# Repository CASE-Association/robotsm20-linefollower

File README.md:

# Blitz V2
Project repository for the line follower **Blitz V2** to compete in Robot SM 2020. Last years robot was [Blitz V1](https://github.com/caselabbet/robotsm19-linefollower).

Below is a rendered version of **Blitz V2**.

## Goals 
- Utilize more advanced control algorithm.
    - Acceleration control
        - Speed trajectory planner
    - Speed control
        - PID + Anti windup + Active damping
    - Position control
        - PID + Anti windup + Active damping
    - State space model + LQG controller (*optional*)
    - MPC - Model Predictive Conrol (*optional)*
- Map race track + Path planner (*optional*)
- Beat last years result and take 1st place. (*not optional*) 
- Added hardware and improvements
    - Use of suction/exhuast fans
    - Single PCB
    - Bluetooth communication
    - High power motors (11W vs 1/2W)
 
## Directories 
```
robotsm20-linefollower
├── datasheets      
├── hardware        
│   ├── cad         # 3D models
│   │   └── stl     # 3D print files
│   └── pcb         # Schematic, layout and production files
├── img             
├── simulation      # Matlab + simulink simulations
└── software
    ├── Inc         # C header files
    └── Src         # C source files
  ```

## Development enviroment
The microcontroller configuration for peripherals such as ADC, GPIO, TIM, Clock etc. is set up via [STM32CubeMX](https://www.st.com/en/development-tools/stm32cubemx.html) (GUI) and is then ported to a PlatformIO project with the [stm32pio](https://github.com/ussserrr/stm32pio) command. The software is developed in the [VS Code](https://code.visualstudio.com/) IDE with the [PlatformIO](https://platformio.org/) plugin.

This makes it possible to generate base code for initialization of peripherals with the powerful configurator <b>STM32CubeMX</b> but also use the great </b>PlatformIO + VS code</b> ecosystem to manage compiling, uploading, debugging and scripting tasks.

## Installation
In order to update configuration in <b>STM32CubeMX</b> and then update <b>PlatformIO</b> project you need to set up your development enviroment:
 - Create a `boards` directory in your platformio home folder:
    - Unix: `~/.platformio/`
    - Windows: `%HOMEPATH%\.platformio`
 - Copy the custom board `stm32f405rg.json` to the newly created `boards` directory.
 - Verify that the board has been added by running `platformio boards stm32` and find the stm32f405 board.
    <details>
    <summary><b>Common problems</b></summary>

    - If it is not in the list, make sure you put the `boards` in the correct folder and spelled it right.

    - [platformio is not recognized as an internal command](https://docs.platformio.org/en/latest/installation.html#install-shell-commands) 
    </details>
- Rename the file `stm32pio_template.ini` inside the `software` folder to `stm32pio.ini`and fill it out according to the template:
 ```` ini
[app]
java_cmd = java
platformio_cmd = platformio
cubemx_cmd = path/to/cubemx_program

[project]
cubemx_script_content = config load path/to/cubemx_file.ioc
	generate code path/to/projectFolder
	exit
platformio_ini_patch_content = [platformio]
	include_dir = Inc
	src_dir = Src
ioc_file = path/to/cubemxfile.ioc
board = stm32f405rg
````

<details><summary>Unix example</summary>

``` ini
[app]
java_cmd = java
platformio_cmd = platformio
cubemx_cmd = /Applications/STMicroelectronics/STM32CubeMX.app/Contents/Resources/STM32CubeMX

[project]
cubemx_script_content = config load /Users/isakaslund/Documents/code/robotsm20-linefollower/software/software.ioc
	generate code /Users/isakaslund/Documents/code/robotsm20-linefollower/software/
	exit
platformio_ini_patch_content = [platformio]
	include_dir = Inc
	src_dir = Src
ioc_file = /Users/isakaslund/Documents/code/robotsm20-linefollower/software/software.ioc
board = stm32f405rg

```
</details>
<details><summary>Windows example</summary>

``` ini
[app]
java_cmd = java
platformio_cmd = platformio
cubemx_cmd = C:/Program Files/STMicroelectronics/STM32Cube/STM32CubeMX/STM32CubeMX.exe

[project]
cubemx_script_content = config load C:\Users\Isak\Documents\GitHub\robotsm20-linefollower\software\software.ioc
	generate code C:\Users\Isak\Documents\GitHub\robotsm20-linefollower
	exit
platformio_ini_patch_content = [platformio]
	include_dir = Inc
	src_dir = Src
	
ioc_file = C:\Users\Isak\Documents\GitHub\robotsm20-linefollower\software\software.ioc
board = stm32f405rg

```

</details>

Your `software` folder should look this when finished
```
software
├── Inc
│   ├── header_files.h
│   ├── ...
├── Src
│   ├── c_files.c
│   ├── ...
├── platformio.ini
├── software.ioc
├── stm32f405rg.json
└── stm32pio.ini
```

## Usage
#### Configuration change
Change configuration of peripherals in the STM32CubeMX file `software.ioc` and then save project. **DO NOT** click the `generate code` button. 

To then update the `platformio` project run the following command inside the `software` folder:
``` sh
$ stm32pio generate
```

#### Building
Use the platform build task or press the "✓" button in the bottom left in VS code

#### Uploading
A programmer called [ST-Link](https://docs.platformio.org/en/latest/plus/debug-tools/stlink.html) is needed to upload by connecting it to the SWD pins found on the robot.

Use the platform io upload task or press the "⇨" button in the bottom left in vs code. 

#### Debugging
With the STM32 processesor you can do more then `Serial.println()` debugging over serial.
You can step debug, inspect/change variables, set breakpoints and more by using the dedicated debugger/programmer `ST-Link` and the [platformio unified debugger](https://docs.platformio.org/en/latest/plus/debugging.html).

When setup you can start debugging by going to `Debug` -> `Start debugging` in the menu bar. 

## Contributors
  - Isak Åslund - aslundisak@gmail.com
  - Oskar Johansson - oskaj@student.chalmers.se

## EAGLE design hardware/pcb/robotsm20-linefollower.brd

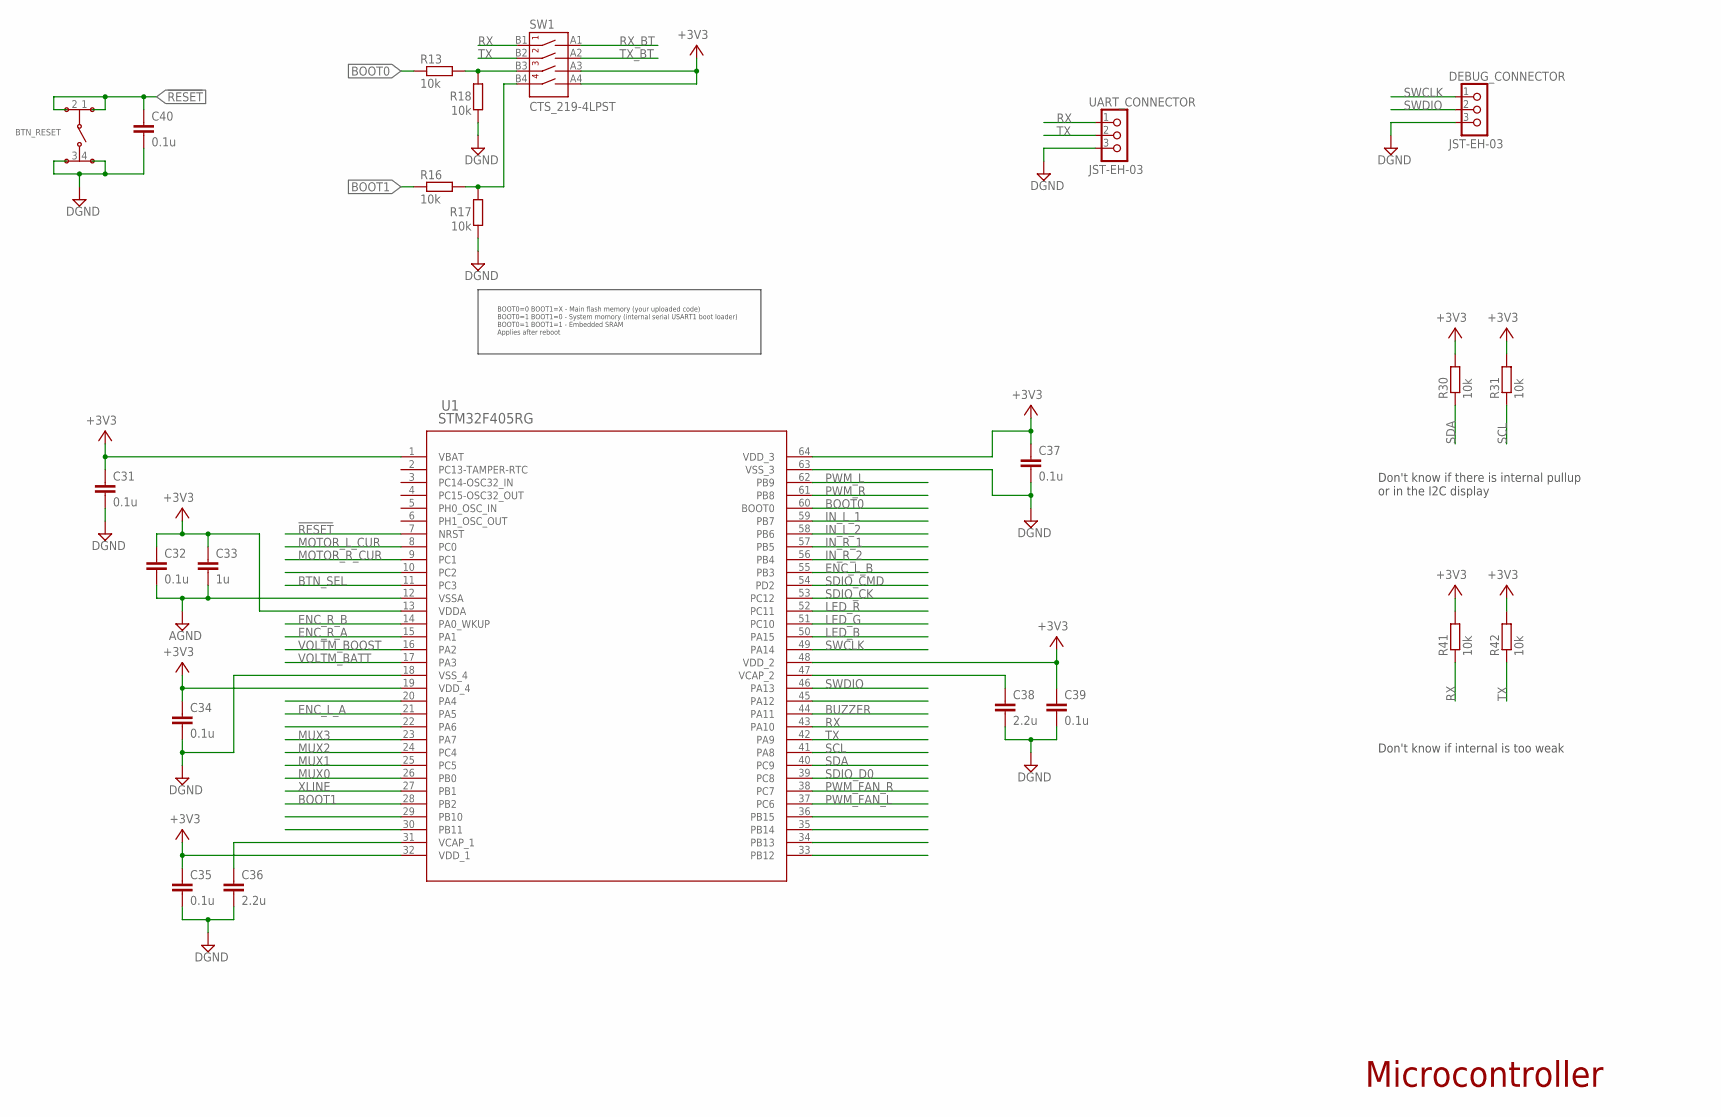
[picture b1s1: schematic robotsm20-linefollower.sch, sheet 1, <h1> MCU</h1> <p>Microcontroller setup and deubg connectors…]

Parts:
BTN_RESET: TSM2JSMA
C31, C32, C34, C35, C37, C39, C40: 0.1u; C0603
C33: 1u; C0603
C36, C38: 2.2u; C0603
DEBUG_CONNECTOR: JST-EH-03; B3B-EH
R13, R16, R17, R18, R30, R31, R41, R42: 10k; R0603
SW1: CTS_219-4LPST; DIPSWITCH_4P_SMD
U1: STM32F405RG; LQFP-64
UART_CONNECTOR: JST-EH-03; B3B-EH

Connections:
!RESET: BTN_RESET.1, BTN_RESET.2, C40.1, U1.7 (NRST)
+3V3: C31.1, C32.1, C33.1, C34.1, C35.1, C37.1, C39.1, R30.1, R31.1, R41.1, R42.1, SW1.A3, SW1.A4, U1.1 (VBAT), U1.13 (VDDA), U1.19 (VDD_4), U1.32 (VDD_1), U1.48 (VDD_2), U1.64 (VDD_3); also elsewhere on the board
AGND: C32.2, C33.2, U1.12 (VSSA); also elsewhere on the board
BOOT0: R13.2, U1.60 (BOOT0)
BOOT1: R16.1, U1.28 (PB2)
BTN_SEL: U1.11 (PC3); also elsewhere on the board
BUZZER: U1.44 (PA11); also elsewhere on the board
DGND: BTN_RESET.3, BTN_RESET.4, C31.2, C34.2, C35.2, C36.2, C37.2, C38.2, C39.2, C40.2, DEBUG_CONNECTOR.3, R17.1, R18.1, U1.18 (VSS_4), U1.63 (VSS_3), UART_CONNECTOR.3; also elsewhere on the board
ENC_L_A: U1.21 (PA5); also elsewhere on the board
ENC_L_B: U1.55 (PB3); also elsewhere on the board
ENC_R_A: U1.15 (PA1); also elsewhere on the board
ENC_R_B: U1.14 (PA0_WKUP); also elsewhere on the board
IN_L_1: U1.59 (PB7); also elsewhere on the board
IN_L_2: U1.58 (PB6); also elsewhere on the board
IN_R_1: U1.57 (PB5); also elsewhere on the board
IN_R_2: U1.56 (PB4); also elsewhere on the board
LED_B: U1.50 (PA15); also elsewhere on the board
LED_G: U1.51 (PC10); also elsewhere on the board
LED_R: U1.52 (PC11); also elsewhere on the board
MOTOR_L_CUR: U1.8 (PC0); also elsewhere on the board
MOTOR_R_CUR: U1.9 (PC1); also elsewhere on the board
MUX0: U1.26 (PB0); also elsewhere on the board
MUX1: U1.25 (PC5); also elsewhere on the board
MUX2: U1.24 (PC4); also elsewhere on the board
MUX3: U1.23 (PA7); also elsewhere on the board
unnamed: R16.2, R17.2, SW1.B4
unnamed: R13.1, R18.2, SW1.B3
unnamed: C36.1, U1.31 (VCAP_1)
unnamed: C38.1, U1.47 (VCAP_2)
PWM_FAN_L: U1.37 (PC6); also elsewhere on the board
PWM_FAN_R: U1.38 (PC7); also elsewhere on the board
PWM_L: U1.62 (PB9); also elsewhere on the board
PWM_R: U1.61 (PB8); also elsewhere on the board
RX: R41.2, SW1.B1, U1.43 (PA10), UART_CONNECTOR.1
RX_BT: SW1.A1; also elsewhere on the board
SCL: R31.2, U1.41 (PA8); also elsewhere on the board
SDA: R30.2, U1.40 (PC9); also elsewhere on the board
SDIO_CK: U1.53 (PC12); also elsewhere on the board
SDIO_CMD: U1.54 (PD2); also elsewhere on the board
SDIO_D0: U1.39 (PC8); also elsewhere on the board
SWCLK: DEBUG_CONNECTOR.1, U1.49 (PA14)
SWDIO: DEBUG_CONNECTOR.2, U1.46 (PA13)
TX: R42.2, SW1.B2, U1.42 (PA9), UART_CONNECTOR.2
TX_BT: SW1.A2; also elsewhere on the board
VOLTM_BATT: U1.17 (PA3); also elsewhere on the board
VOLTM_BOOST: U1.16 (PA2); also elsewhere on the board
XLINE: U1.27 (PB1); also elsewhere on the board

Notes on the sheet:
Microcontroller
BOOT0=0 BOOT1=X - Main flash memory (your uploaded code) BOOT0=1 BOOT1=0 - System momory (internal serial USART1 boot loader) BOOT0=1 BOOT1=1 - Embedded SRAM Applies after reboot
Don't know if there is internal pullup or in the I2C display
Don't know if internal is too weak

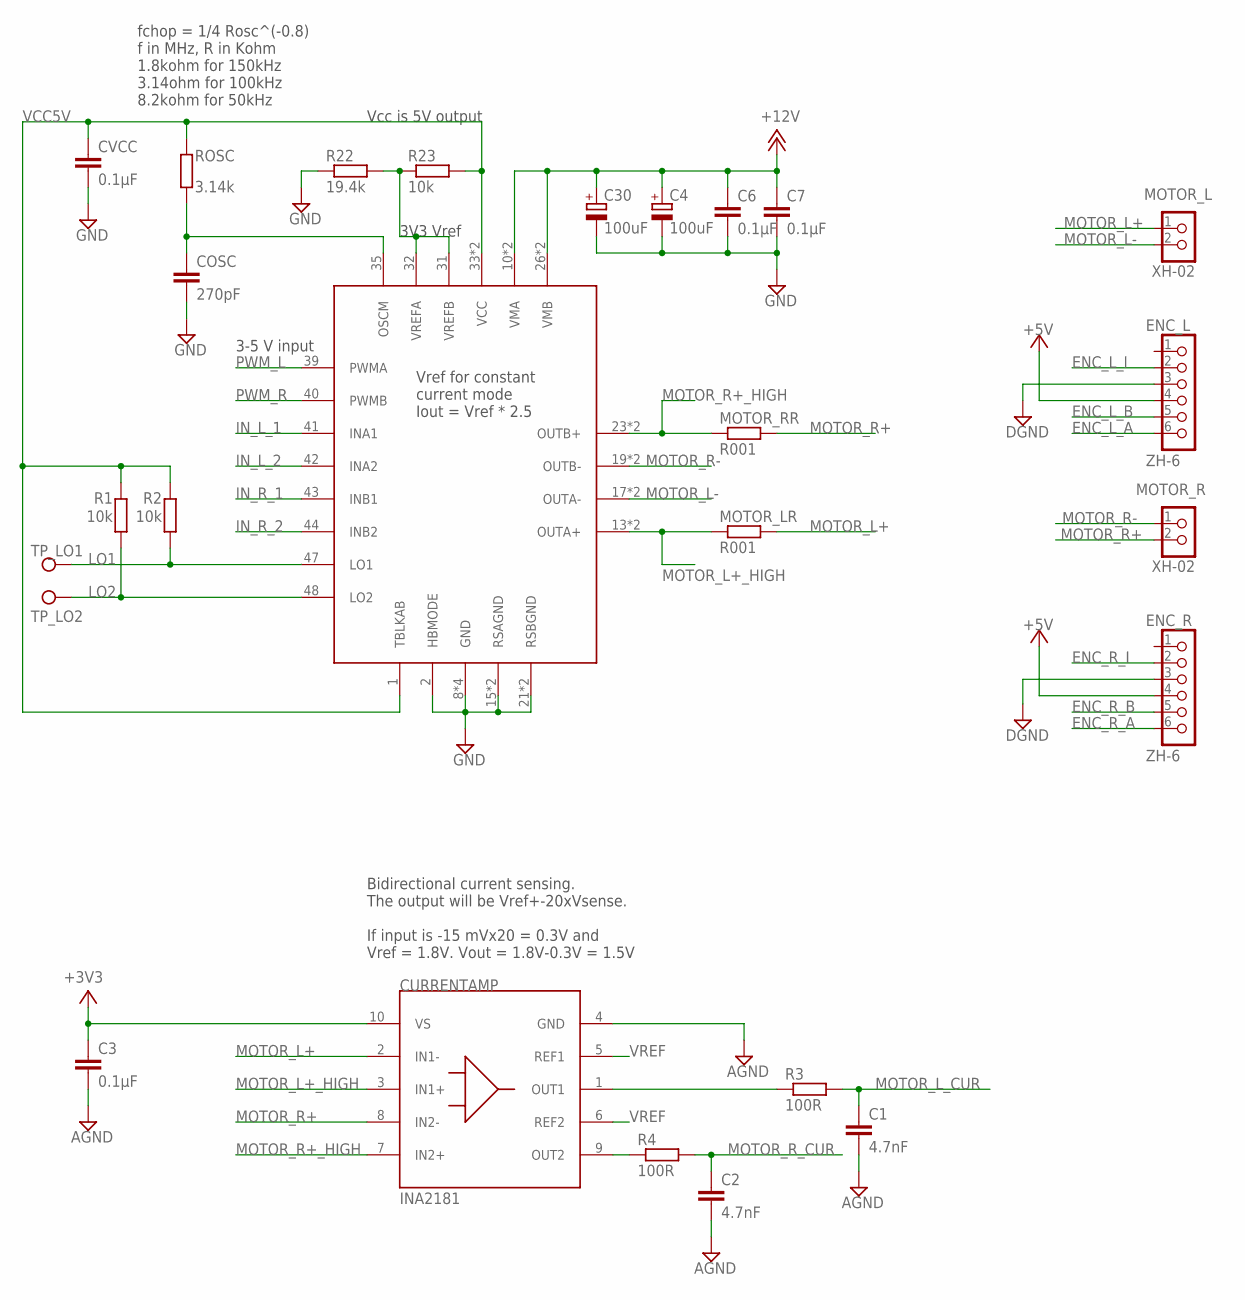
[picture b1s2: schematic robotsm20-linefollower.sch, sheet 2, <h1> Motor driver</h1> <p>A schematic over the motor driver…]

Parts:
C1, C2: 4.7nF; C0603
C3: 0.1µF; C0603
C4, C30: 100uF; CAPAE660X700N
C6, C7: 0.1µF; C0805
COSC: 270pF; C0603
CURRENTAMP: INA2181; SOP50P490X110-10N
CVCC: 0.1µF; C0603
ENC_L: ZH-6; B6B-ZR
ENC_R: ZH-6; B6B-ZR
MOTORDRIVER: TB67H420FTG; QFN50P700X700X100-49T550N
MOTOR_L: XH-02; JST-XH-02
MOTOR_LR: R001; R2512W
MOTOR_R: XH-02; JST-XH-02
MOTOR_RR: R001; R2512W
R1, R2, R23: 10k; R0603
R3, R4: 100R; R0603
R22: 19.4k; R0603
ROSC: 3.14k; R0603
TP_LO1, TP_LO2: TEST-POINT3X5; PAD.03X.05

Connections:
+3V3: C3.1, CURRENTAMP.10 (VS); also elsewhere on the board
+5V: ENC_L.4, ENC_R.4; also elsewhere on the board
+12V: C4.1 (+), C6.1, C7.1, C30.1 (+), MOTORDRIVER.10 (VMA), MOTORDRIVER.11 (VMA), MOTORDRIVER.26 (VMB), MOTORDRIVER.27 (VMB); also elsewhere on the board
AGND: C1.2, C2.2, C3.2, CURRENTAMP.4 (GND); also elsewhere on the board
DGND: ENC_L.3, ENC_R.3; also elsewhere on the board
ENC_L_A: ENC_L.6; also elsewhere on the board
ENC_L_B: ENC_L.5; also elsewhere on the board
ENC_L_I: ENC_L.2
ENC_R_A: ENC_R.6; also elsewhere on the board
ENC_R_B: ENC_R.5; also elsewhere on the board
ENC_R_I: ENC_R.2
GND: C4.2 (-), C6.2, C7.2, C30.2 (-), COSC.2, CVCC.2, MOTORDRIVER.2 (HBMODE), MOTORDRIVER.8 (GND), MOTORDRIVER.15 (RSAGND), MOTORDRIVER.16 (RSAGND), MOTORDRIVER.21 (RSBGND), MOTORDRIVER.22 (RSBGND), MOTORDRIVER.29 (GND), MOTORDRIVER.30 (GND), MOTORDRIVER.49 (GND), R22.1; also elsewhere on the board
IN_L_1: MOTORDRIVER.41 (INA1); also elsewhere on the board
IN_L_2: MOTORDRIVER.42 (INA2); also elsewhere on the board
IN_R_1: MOTORDRIVER.43 (INB1); also elsewhere on the board
IN_R_2: MOTORDRIVER.44 (INB2); also elsewhere on the board
LO1: MOTORDRIVER.47 (LO1), R2.1, TP_LO1.P$1
LO2: MOTORDRIVER.48 (LO2), R1.1, TP_LO2.P$1
MOTOR_L+: CURRENTAMP.2 (IN1-), MOTOR_L.1, MOTOR_LR.2
MOTOR_L+_HIGH: CURRENTAMP.3 (IN1+), MOTORDRIVER.13 (OUTA+), MOTORDRIVER.14 (OUTA+), MOTOR_LR.1
MOTOR_L-: MOTORDRIVER.17 (OUTA-), MOTORDRIVER.18 (OUTA-), MOTOR_L.2
MOTOR_L_CUR: C1.1, R3.2; also elsewhere on the board
MOTOR_R+: CURRENTAMP.8 (IN2-), MOTOR_R.2, MOTOR_RR.2
MOTOR_R+_HIGH: CURRENTAMP.7 (IN2+), MOTORDRIVER.23 (OUTB+), MOTORDRIVER.24 (OUTB+), MOTOR_RR.1
MOTOR_R-: MOTORDRIVER.19 (OUTB-), MOTORDRIVER.20 (OUTB-), MOTOR_R.1
MOTOR_R_CUR: C2.1, R4.2; also elsewhere on the board
unnamed: CURRENTAMP.9 (OUT2), R4.1
unnamed: CURRENTAMP.1 (OUT1), R3.1
unnamed: MOTORDRIVER.31 (VREFB), MOTORDRIVER.32 (VREFA), R22.2, R23.1
unnamed: COSC.1, MOTORDRIVER.35 (OSCM), ROSC.1
PWM_L: MOTORDRIVER.39 (PWMA); also elsewhere on the board
PWM_R: MOTORDRIVER.40 (PWMB); also elsewhere on the board
VCC5V: CVCC.1, MOTORDRIVER.1 (TBLKAB), MOTORDRIVER.33 (VCC), MOTORDRIVER.34 (VCC), R1.2, R2.2, R23.2, ROSC.2
VREF: CURRENTAMP.5 (REF1), CURRENTAMP.6 (REF2); also elsewhere on the board

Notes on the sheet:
Bidirectional current sensing. The output will be Vref+-20xVsense. If input is -15 mVx20 = 0.3V and Vref = 1.8V. Vout = 1.8V-0.3V = 1.5V
3-5 V input
Vcc is 5V output
3V3 Vref
fchop = 1/4 Rosc^(-0.8) f in MHz, R in Kohm 1.8kohm for 150kHz 3.14ohm for 100kHz 8.2kohm for 50kHz
Vref for constant current mode Iout = Vref * 2.5

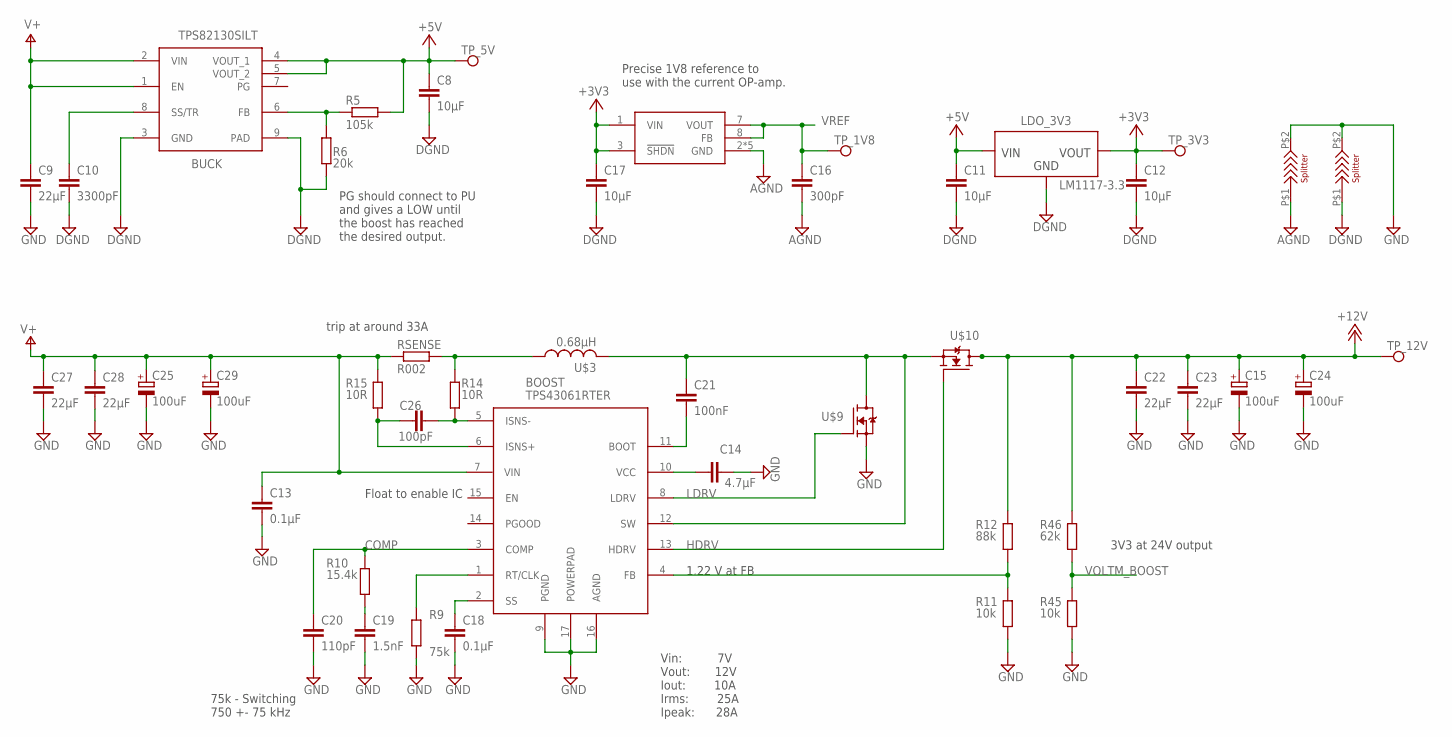
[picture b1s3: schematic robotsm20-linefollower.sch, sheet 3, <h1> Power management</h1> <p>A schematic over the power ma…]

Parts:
BOOST: TPS43061RTER; QFN50P300X300X80-17N
BUCK: TPS82130SILT
C8, C11, C12, C17: 10µF; C0603
C9, C22, C23, C27, C28: 22µF; C0805
C10: 3300pF; C0805
C13, C18: 0.1µF; C0805
C14: 4.7µF; C0805
C15, C24, C25, C29: 100uF; CAPAE660X700N
C16: 300pF; C0603
C19: 1.5nF; C0805
C20: 110pF; C0805
C21: 100nF; C0805
C26: 100pF; C0805
LDO_3V3: LM1117-3.3; SOT230P700X180-4
LDO_VREF_1V8: MCP1501T-XXE; SON50P200X200X80-9T80X120N
R5: 105k; R0603
R6: 20k; R0603
R9: 75k; R0603
R10: 15.4k; R0603
R11, R45: 10k; R0603
R12: 88k; R0603
R14, R15: 10R; R0603
R46: 62k; R0603
RSENSE: R002; R2512W
TP_1V8, TP_3V3, TP_5V, TP_12V: TEST_POINTPAD_HOLE; PAD_HOLE
U$3: 0.68µH; INDM135125X330N
U$4, U$6: SPLITTER
U$9, U$10: CSD17301Q5A; Q5A

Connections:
+3V3: C12.1, C17.1, LDO_3V3.2 (VOUT), LDO_3V3.4 (VOUT), LDO_VREF_1V8.1 (VIN), LDO_VREF_1V8.3 (!SHDN!), TP_3V3.P$1; also elsewhere on the board
+5V: BUCK.4 (VOUT_1), BUCK.5 (VOUT_2), C8.1, C11.1, LDO_3V3.3 (VIN), R5.2, TP_5V.P$1; also elsewhere on the board
+12V: C15.1 (+), C22.1, C23.1, C24.1 (+), R12.2, R46.2, TP_12V.P$1, U$10.5 (D), U$10.6 (D), U$10.7 (D), U$10.8 (D), U$10.9 (D); also elsewhere on the board
AGND: C16.2, LDO_VREF_1V8.2 (GND), LDO_VREF_1V8.4 (GND), LDO_VREF_1V8.5 (GND), LDO_VREF_1V8.6 (GND), LDO_VREF_1V8.9 (GND), U$4.P$1 (1); also elsewhere on the board
COMP: BOOST.3 (COMP), C20.1, R10.2
DGND: BUCK.3 (GND), BUCK.9 (PAD), C8.2, C10.2, C11.2, C12.2, C17.2, LDO_3V3.1 (GND), R6.1, U$6.P$1 (1); also elsewhere on the board
GND: BOOST.9 (PGND), BOOST.16 (AGND), BOOST.17 (POWERPAD), C9.2, C13.2, C14.2, C15.2 (-), C18.2, C19.2, C20.2, C22.2, C23.2, C24.2 (-), C25.2 (-), C27.2, C28.2, C29.2 (-), R9.1, R11.1, R45.1, U$4.P$2 (2), U$6.P$2 (2), U$9.1 (S), U$9.2 (S), U$9.3 (S); also elsewhere on the board
HDRV: BOOST.13 (HDRV), U$10.4 (G)
LDRV: BOOST.8 (LDRV), U$9.4 (G)
unnamed: BOOST.10 (VCC), C14.1
unnamed: BUCK.8 (SS/TR), C10.1
unnamed: BUCK.6 (FB), R5.1, R6.2
unnamed: BOOST.1 (RT/CLK), R9.2
unnamed: BOOST.2 (SS), C18.1
unnamed: C19.1, R10.1
unnamed: BOOST.11 (BOOT), C21.2
unnamed: R14.2, RSENSE.2, U$3.1
unnamed: BOOST.12 (SW), C21.1, U$3.2, U$9.5 (D), U$9.6 (D), U$9.7 (D), U$9.8 (D), U$9.9 (D), U$10.1 (S), U$10.2 (S), U$10.3 (S)
unnamed: BOOST.4 (FB), R11.2, R12.1
unnamed: BOOST.5 (ISNS-), C26.2, R14.1
unnamed: BOOST.6 (ISNS+), C26.1, R15.1
V+: BOOST.7 (VIN), BUCK.1 (EN), BUCK.2 (VIN), C9.1, C13.1, C25.1 (+), C27.1, C28.1, C29.1 (+), R15.2, RSENSE.1; also elsewhere on the board
VOLTM_BOOST: R45.2, R46.1; also elsewhere on the board
VREF: C16.1, LDO_VREF_1V8.7 (VOUT), LDO_VREF_1V8.8 (FB), TP_1V8.P$1; also elsewhere on the board

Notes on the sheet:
PG should connect to PU and gives a LOW until the boost has reached the desired output.
Precise 1V8 reference to use with the current OP-amp.
75k - Switching 750 +- 75 kHz
1.22 V at FB
trip at around 33A
Vin: 7V Vout: 12V Iout: 10A Irms: 25A Ipeak: 28A
3V3 at 24V output
Float to enable IC

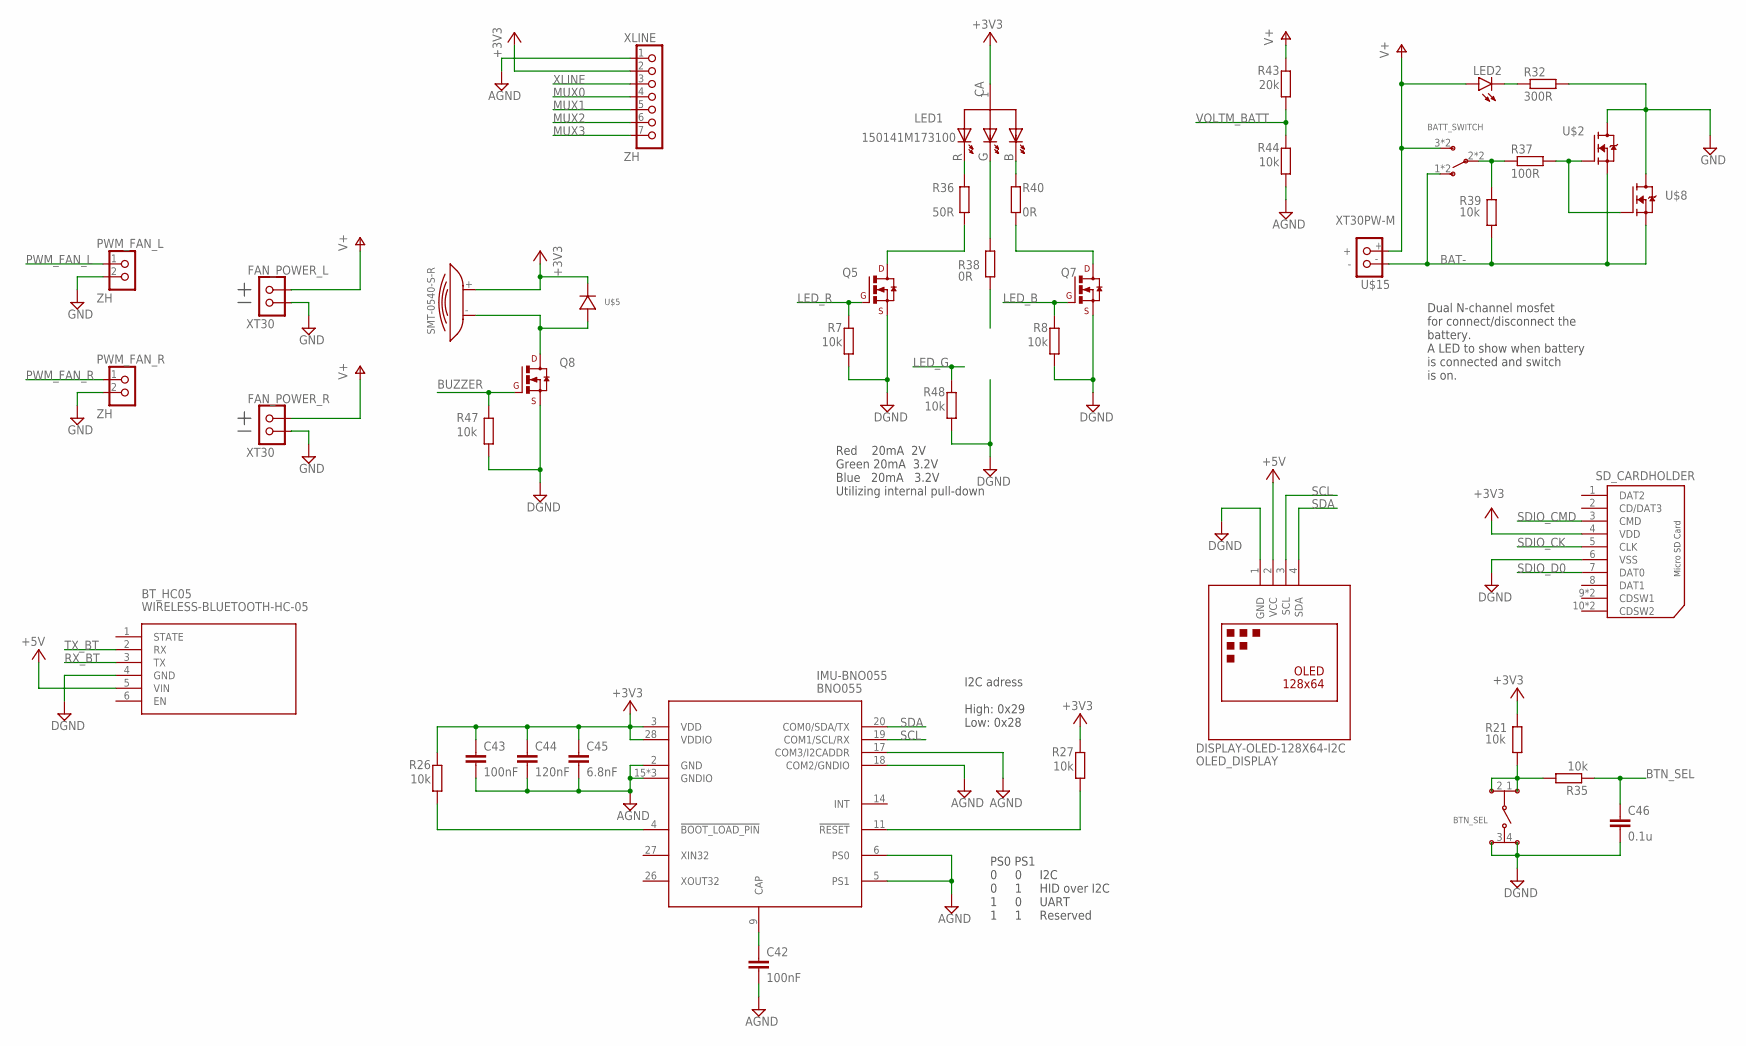
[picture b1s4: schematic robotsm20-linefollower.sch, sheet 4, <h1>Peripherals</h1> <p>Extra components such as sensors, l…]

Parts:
BATT_SWITCH: JS202011AQN
BTN_SEL: TSM2JSMA
BT_HC05: WIRELESS-BLUETOOTH-HC-05
C42, C43: 100nF; C0603
C44: 120nF; C0603
C45: 6.8nF; C0603
C46: 0.1u; C0603
FAN_POWER_L: XT30
FAN_POWER_R: XT30
IMU-BNO055: BNO055
LED1: 150141M173100
LED2: LEDCHIPLED_0603; CHIPLED_0603
OLED_DISPLAY: DISPLAY-OLED-128X64-I2C
PWM_FAN_L: ZH; B2B-ZR
PWM_FAN_R: ZH; B2B-ZR
Q5, Q7, Q8: BSS138LT3G; SOT23
R7, R8, R21, R26, R27, R35, R39, R44, R47, R48: 10k; R0603
R32: 300R; R0603
R36: 50R; R0603
R37: 100R; R0603
R38, R40: 0R; R0603
R43: 20k; R0603
SD_CARDHOLDER: MICRO_SD_WE_693071010811; 693071010811
U$1: SMT-0540-S-R
U$2, U$8: CSD17301Q5A; Q5A
U$5: DIODE_1N4148WX; 1N4148WX_SOD-323-2
U$15: XT30PW-M
XLINE: ZH; B7B-ZR

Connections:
+3V3: C43.1, C44.1, C45.1, IMU-BNO055.3 (VDD), IMU-BNO055.28 (VDDIO), LED1.1 (CA), R21.1, R26.2, R27.2, SD_CARDHOLDER.4 (VDD), U$1.+, U$5.- (-_CATHODE), XLINE.2; also elsewhere on the board
+5V: BT_HC05.5 (VIN), OLED_DISPLAY.2 (VCC); also elsewhere on the board
AGND: C42.2, C43.2, C44.2, C45.2, IMU-BNO055.2 (GND), IMU-BNO055.5 (PS1), IMU-BNO055.6 (PS0), IMU-BNO055.15 (GNDIO), IMU-BNO055.16 (GNDIO), IMU-BNO055.17 (COM3/I2CADDR), IMU-BNO055.18 (COM2/GNDIO), IMU-BNO055.25 (GNDIO), R44.2, XLINE.1; also elsewhere on the board
BAT-: BATT_SWITCH.1 (NC), BATT_SWITCH.4 (NC), R39.1, U$2.1 (S), U$2.2 (S), U$2.3 (S), U$8.1 (S), U$8.2 (S), U$8.3 (S), U$15.-
BTN_SEL: C46.1, R35.1; also elsewhere on the board
BUZZER: Q8.1 (G), R47.1; also elsewhere on the board
DGND: BTN_SEL.3, BTN_SEL.4, BT_HC05.4 (GND), C46.2, OLED_DISPLAY.1 (GND), Q5.2 (S), Q7.2 (S), Q8.2 (S), R7.1, R8.1, R47.2, R48.1, SD_CARDHOLDER.6 (VSS); also elsewhere on the board
GND: FAN_POWER_L.NEG-, FAN_POWER_R.NEG-, PWM_FAN_L.2, PWM_FAN_R.2, R32.1, U$2.5 (D), U$2.6 (D), U$2.7 (D), U$2.8 (D), U$2.9 (D), U$8.5 (D), U$8.6 (D), U$8.7 (D), U$8.8 (D), U$8.9 (D); also elsewhere on the board
LED_B: Q7.1 (G), R8.2; also elsewhere on the board
LED_G: R48.2; also elsewhere on the board
LED_R: Q5.1 (G), R7.2; also elsewhere on the board
MUX0: XLINE.4; also elsewhere on the board
MUX1: XLINE.5; also elsewhere on the board
MUX2: XLINE.6; also elsewhere on the board
MUX3: XLINE.7; also elsewhere on the board
unnamed: BTN_SEL.1, BTN_SEL.2, R21.2, R35.2
unnamed: IMU-BNO055.11 (!RESET!), R27.1
unnamed: C42.1, IMU-BNO055.9 (CAP)
unnamed: Q8.3 (D), U$1.-, U$5.+ (+_ANODE)
unnamed: IMU-BNO055.4 (!BOOT_LOAD_PIN!), R26.1
unnamed: LED2.C, R32.2
unnamed: LED1.3 (R), R36.2
unnamed: R37.1, U$2.4 (G), U$8.4 (G)
unnamed: LED1.4 (G), R38.2
unnamed: LED1.2 (B), R40.2
unnamed: Q5.3 (D), R36.1
unnamed: BATT_SWITCH.2 (COM), BATT_SWITCH.5 (COM), R37.2, R39.2
unnamed: Q7.3 (D), R40.1
PWM_FAN_L: PWM_FAN_L.1; also elsewhere on the board
PWM_FAN_R: PWM_FAN_R.1; also elsewhere on the board
RX_BT: BT_HC05.3 (TX); also elsewhere on the board
SCL: IMU-BNO055.19 (COM1/SCL/RX), OLED_DISPLAY.3 (SCL); also elsewhere on the board
SDA: IMU-BNO055.20 (COM0/SDA/TX), OLED_DISPLAY.4 (SDA); also elsewhere on the board
SDIO_CK: SD_CARDHOLDER.5 (CLK); also elsewhere on the board
SDIO_CMD: SD_CARDHOLDER.3 (CMD); also elsewhere on the board
SDIO_D0: SD_CARDHOLDER.7 (DAT0); also elsewhere on the board
TX_BT: BT_HC05.2 (RX); also elsewhere on the board
V+: BATT_SWITCH.3 (NO), BATT_SWITCH.6 (NO), FAN_POWER_L.POS+, FAN_POWER_R.POS+, LED2.A, R43.1, U$15.+; also elsewhere on the board
VOLTM_BATT: R43.2, R44.1; also elsewhere on the board
XLINE: XLINE.3; also elsewhere on the board

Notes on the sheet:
I2C adress High: 0x29 Low: 0x28
Dual N-channel mosfet for connect/disconnect the battery. A LED to show when battery is connected and switch is on.
Red 20mA 2V Green 20mA 3.2V Blue 20mA 3.2V Utilizing internal pull-down
PS0 PS1 0 0 I2C 0 1 HID over I2C 1 0 UART 1 1 Reserved

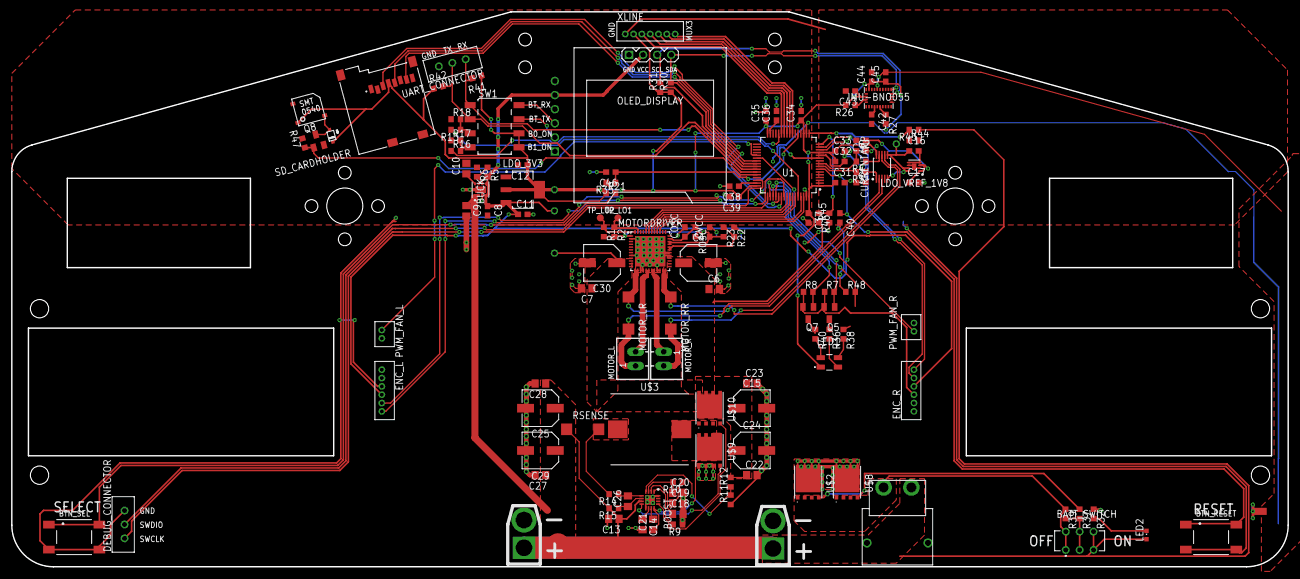
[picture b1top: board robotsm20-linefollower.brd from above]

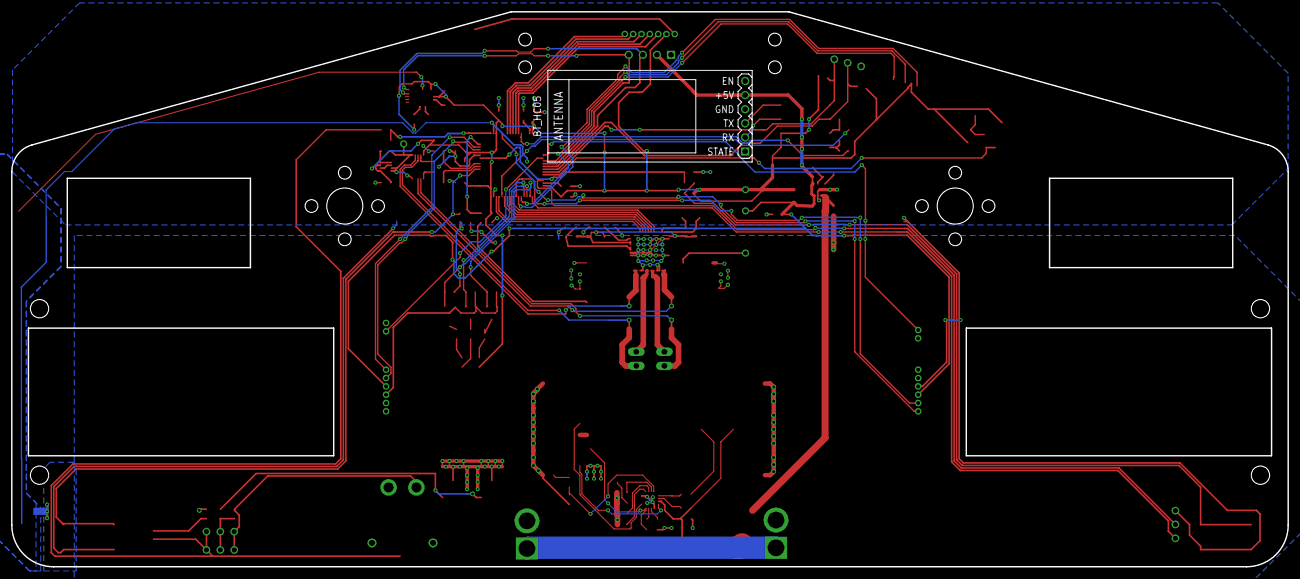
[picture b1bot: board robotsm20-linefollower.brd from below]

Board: 2 copper layers, 230.0 x 100.0 mm, 137 parts (2 on the bottom side), 94 nets.

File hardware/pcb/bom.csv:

Qty;Value;Device;Package;Parts;Description;DATASHEET-URL;DESCRIPTION;MANUFACTURER_PART_NUMBER;MOUSER_PART_NUMBER
1;;C-EUC0603;C0603;C47;CAPACITOR, European symbol;;;;
1;;LEDCHIPLED_0603;CHIPLED_0603;LED2;LED;;;;
1;;MICRO_SD_WE_693071010811;6,93071E+11;SD_CARDHOLDER;WR-CRD Micro SD Card Connector Push & Push 8 pins;https://www.we-online.com/catalog/datasheet/693071010811.pdf;;6,93071E+11;
8;0.1u;C-EUC0603;C0603;C31, C32, C34, C35, C37, C39, C40, C46;CAPACITOR, European symbol;;;;
2;0.1µF;C-EUC0603;C0603;C3, CVCC;CAPACITOR, European symbol;;;;
4;0.1µF;C-EUC0805;C0805;C6, C7, C13, C18;CAPACITOR, European symbol;;;;
1;0.68µH;SRP1238A-XXXX;INDM135125X330N;U$3;Inductor;;;;
2;0R;R-EU_R0603;R0603;R38, R40;RESISTOR, European symbol;;;;
1;1.5nF;C-EUC0805;C0805;C19;CAPACITOR, European symbol;;;;
1;100;R-EU_R0603;R0603;R37;RESISTOR, European symbol;;;;
2;100R;R-EU_R0603;R0603;R3, R4;RESISTOR, European symbol;;;;
2;100nF;C-EUC0603;C0603;C42, C43;CAPACITOR, European symbol;;;;
1;100nF;C-EUC0805;C0805;C21;CAPACITOR, European symbol;;;;
1;100pF;C-EUC0805;C0805;C26;CAPACITOR, European symbol;;;;
6;100uF;WCAP-ASLL-WEWCAP-ASLL;CAPAE660X700N;C4, C15, C24, C25, C29, C30;;;;;
1;105k;R-EU_R0603;R0603;R5;RESISTOR, European symbol;;;;
2;10R;R-EU_R0603;R0603;R14, R15;RESISTOR, European symbol;;;;
23;10k;R-EU_R0603;R0603;R1, R2, R7, R8, R11, R13, R16, R17, R18, R21, R23, R26, R27, R30, R31, R35, R39, R41, R42, R44, R45, R47, R48;RESISTOR, European symbol;;;;
1;110pF;C-EUC0805;C0805;C20;CAPACITOR, European symbol;;;;
1;120nF;C-EUC0603;C0603;C44;CAPACITOR, European symbol;;;;
1;15.4k;R-EU_R0603;R0603;R10;RESISTOR, European symbol;;;;
1;150141M173100;150141M173100;150141M173100;LED1;Wurth Elektronik 150141M173100 Common Anode RGB LED;;;;
1;19.4k;R-EU_R0603;R0603;R22;RESISTOR, European symbol;;;;
1;1u;C-EUC0603;C0603;C33;CAPACITOR, European symbol;;;;
2;2.2u;C-EUC0603;C0603;C36, C38;CAPACITOR, European symbol;;;;
2;20k;R-EU_R0603;R0603;R6, R43;RESISTOR, European symbol;;;;
4;22µF;C-EUC0603;C0603;C8, C11, C12, C17;CAPACITOR, European symbol;;;;
5;22µF;C-EUC0805;C0805;C9, C22, C23, C27, C28;CAPACITOR, European symbol;;;;
1;270pF;C-EUC0603;C0603;COSC;CAPACITOR, European symbol;;;;
1;3.14k;R-EU_R0603;R0603;ROSC;RESISTOR, European symbol;;;;
1;300R;R-EU_R0603;R0603;R32;RESISTOR, European symbol;;;;
1;300pF;C-EUC0603;C0603;C16;CAPACITOR, European symbol;;;;
1;3300pF;C-EUC0805;C0805;C10;CAPACITOR, European symbol;;;;
2;4.7nF;C-EUC0603;C0603;C1, C2;CAPACITOR, European symbol;;;;
1;4.7µF;C-EUC0805;C0805;C14;CAPACITOR, European symbol;;;;
1;50R;R-EU_R0603;R0603;R36;RESISTOR, European symbol;;;;
1;6.8nF;C-EUC0603;C0603;C45;CAPACITOR, European symbol;;;;
1;62k;R-EU_R0603;R0603;R46;RESISTOR, European symbol;;;;
1;75k;R-EU_R0603;R0603;R9;RESISTOR, European symbol;;;;
1;88k;R-EU_R0603;R0603;R12;RESISTOR, European symbol;;;;
1;BNO055;BNO055;BNO055;IMU-BNO055;IMUs - Inertial Measurement Units Absolute Orientation 9-Axis Sensor;;IMUs - Inertial Measurement Units Absolute Orientation 9-Axis Sensor;BNO055;262-BNO055
4;BSS138LT3G;BSS138LT3G;SOT23;Q5, Q6, Q7, Q8;BSS138LT3G N-Channel Mosfet (SOT-23);;;;
4;CSD17301Q5A;CSD17301Q5A;Q5A;U$2, U$8, U$9, U$10;CSD17301Q5A;;;;
1;CTS_219-4LPST;CTS_219-4LPST;DIPSWITCH_4P_SMD;SW1;219-4LPST - Standard 4 position DIP-Switch - SMD;;;;
1;DIODE_1N4148WX;DIODE_1N4148WX;1N4148WX_SOD-323-2;U$5;;;;;
1;DISPLAY-OLED-128X64-I2C;DISPLAY-OLED-128X64-I2C;DISPLAY-OLED-128X64-I2C;OLED_DISPLAY;"OLED 128x63 - I2C - 0.96"";"";"";"";"";"";"";"";"";"";"";"";"";"";"";"";"";"";
1""";INA2181;INA2181;;
1;JS202011AQN;JS202011AQN;JS202011AQN;BATT_SWITCH;JS202011AQN;;;;
2;JST-EH-03;EH_B3B-EH;B3B-EH;DEBUG_CONNECTOR, UART_CONNECTOR;JST EH Connector, through hole, 3 pin, top entry;;;;
1;LM1117-3.3;LM1117-3.3;SOT230P700X180-4;LDO_3V3;LM1117;;;;
1;MCP1501T-XXE;MCP1501T-XXE;SON50P200X200X80-9T80X120N;LDO_VREF_1V8;MCP1501T-XXE;;;;
2;R001;R-EU_R2512W;R2512W;MOTOR_LR, MOTOR_RR;RESISTOR, European symbol;;;;
1;R002;R-EU_R2512W;R2512W;RSENSE;RESISTOR, European symbol;;;;
1;SMT-0540-S-R;SMT-0540-S-R;SMT-0540-S-R;U$1;Magnetic buzzer;;;;
2;SPLITTER;SPLITTER;SPLITTER;U$4, U$6;Used for separating grounds;;;;
1;STM32F405RG;STM32F405RG;LQFP-64;U1;STM32F405RG Microcontroller;;;;
1;TB67H420FTG;TB67H420FTG;QFN50P700X700X100-49T550N;MOTORDRIVER;TB67H420FTG;;;;
2;TEST-POINT3X5;TEST-POINT3X5;PAD.03X.05;TP_LO1, TP_LO2;Test Points;;;;
4;TEST_POINTPAD_HOLE;TEST_POINTPAD_HOLE;PAD_HOLE;TP_1V8, TP_3V3, TP_5V, TP_12V;;;;;
1;TPS43061RTER;TPS43061RTER;QFN50P300X300X80-17N;BOOST;Low Iq, Synchronous Boost Controller with Wide Input Voltage and 5.5V Gate Drive for Low Qg  NexFETs;;Low Iq, Synchronous Boost Controller with Wide Input Voltage and 5.5V Gate Drive for Low Qg  NexFETs;TPS43061RTER;595-TPS43061RTER
1;TPS82130SILT;TPS82130SILT;TPS82130SILT;BUCK;3-A 17V Step-down Converter Module with Integrated Inductor;;3-A 17V Step-down Converter Module with Integrated Inductor;TPS82130SILT;595-TPS82130SILT
2;TSM2JSMA;TSM2JSMA;TSM2JSMA;BTN_RESET, BTN_SEL;FSM2JSMA Tactile SPST switches;;;;
1;WIRELESS-BLUETOOTH-HC-05;WIRELESS-BLUETOOTH-HC-05;WIRELESS-BLUETOOTH-HC-05;BT_HC05;Bluetooth Transceiver Module based on HC-05 board;;;;
2;XH-02;XH-02;JST-XH-02;MOTOR_L, MOTOR_R;JST EX Connector, through hole, 2 pin, top entry;;;;
2;XT30;XT30;XT30;FAN_POWER_L, FAN_POWER_R;XT60 Connector;;;;
1;XT30PW-M;XT30PW-M;XT30PW-M;U$15;;;;;
2;ZH;ZR_B2B-ZR;B2B-ZR;PWM_FAN_L, PWM_FAN_R;JST ZR Connector, through hole, 2 pin, top entry;;;;
1;ZH;ZR_B7B-ZR;B7B-ZR;XLINE;JST ZR Connector, through hole, 7 pin, top entry;;;;
2;ZH-6;ZR_B6B-ZR;B6B-ZR;ENC_L, ENC_R;JST ZR Connector, through hole, 6 pin, top entry;;;;

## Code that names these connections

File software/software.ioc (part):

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Mcu.Name=STM32F405RGTx
Mcu.Package=LQFP64
Mcu.UserName=STM32F405RGTx
PA0-WKUP.GPIOParameters=GPIO_Label
PA0-WKUP.GPIO_Label=ENC_R_B
PA0-WKUP.Signal=S_TIM5_CH1
PA1.GPIOParameters=GPIO_Label
PA1.GPIO_Label=ENC_R_A
PA1.Signal=S_TIM5_CH2
PA10.GPIOParameters=GPIO_Label
PA10.GPIO_Label=RX
PA10.Mode=Asynchronous
PA10.Signal=USART1_RX
PA11.GPIOParameters=GPIO_Label
PA11.GPIO_Label=BUZZER
PA11.Signal=S_TIM1_CH4
PA13.GPIOParameters=GPIO_Label
PA13.GPIO_Label=SWDIO
PA13.Mode=Serial_Wire
PA13.Signal=SYS_JTMS-SWDIO
PA14.GPIOParameters=GPIO_Label
PA14.GPIO_Label=SWCLK
PA14.Mode=Serial_Wire
PA14.Signal=SYS_JTCK-SWCLK
PA15.GPIOParameters=GPIO_PuPd,GPIO_Label
PA15.GPIO_Label=LED_B
PA15.GPIO_PuPd=GPIO_PULLDOWN
PA15.Signal=GPIO_Output
PA2.GPIOParameters=GPIO_Label
PA2.GPIO_Label=VOLTM_BOOST
PA2.Signal=ADCx_IN2
PA3.GPIOParameters=GPIO_Label
PA3.GPIO_Label=VOLTM_BATT
PA3.Signal=ADCx_IN3
PA5.GPIOParameters=GPIO_Label
PA5.GPIO_Label=ENC_L_A
PA5.Signal=S_TIM2_CH1_ETR
PA7.GPIOParameters=GPIO_Label
PA7.GPIO_Label=MUX3
PA7.Signal=GPIO_Output
PA8.GPIOParameters=GPIO_Label
PA8.GPIO_Label=SCL
PA8.Mode=I2C
PA8.Signal=I2C3_SCL
PA9.GPIOParameters=GPIO_Label
PA9.GPIO_Label=TX
PA9.Mode=Asynchronous
PA9.Signal=USART1_TX
PB0.GPIOParameters=GPIO_Label
PB0.GPIO_Label=MUX0
PB0.Signal=GPIO_Output
PB1.GPIOParameters=GPIO_Label
PB1.GPIO_Label=XLINE
PB1.Signal=ADCx_IN9
PB2.GPIOParameters=GPIO_Label
PB2.GPIO_Label=BOOT1
PB2.Signal=GPIO_Output
PB3.GPIOParameters=GPIO_Label
PB3.GPIO_Label=ENC_L_B
PB3.Signal=S_TIM2_CH2
PB4.GPIOParameters=GPIO_Label
PB4.GPIO_Label=MOTOR_R_IN2
PB4.Signal=GPIO_Output
PB5.GPIOParameters=GPIO_Label
PB5.GPIO_Label=MOTOR_R_IN1
PB5.Signal=GPIO_Output
PB6.GPIOParameters=GPIO_Label
PB6.GPIO_Label=MOTOR_L_IN2
PB6.Signal=GPIO_Output
PB7.GPIOParameters=GPIO_Label
PB7.GPIO_Label=MOTOR_L_IN1
PB7.Signal=GPIO_Output
PB8.GPIOParameters=GPIO_Label
PB8.GPIO_Label=MOTOR_R_PWM
PB8.Signal=S_TIM4_CH3
PB9.GPIOParameters=GPIO_Label
PB9.GPIO_Label=MOTOR_L_PWM
PB9.Signal=S_TIM4_CH4
PC0.GPIOParameters=GPIO_Label
PC0.GPIO_Label=MOTOR_L_CURR
PC0.Signal=ADCx_IN10
PC1.GPIOParameters=GPIO_Label
PC1.GPIO_Label=MOTOR_R_CURR
PC1.Signal=ADCx_IN11
PC10.GPIOParameters=GPIO_PuPd,GPIO_Label
PC10.GPIO_Label=LED_G
PC10.GPIO_PuPd=GPIO_PULLDOWN
PC10.Signal=GPIO_Output
PC11.GPIOParameters=GPIO_PuPd,GPIO_Label
PC11.GPIO_Label=LED_R
PC11.GPIO_PuPd=GPIO_PULLDOWN
PC11.Signal=GPIO_Output
PC12.Mode=SD_1_bit
PC12.Signal=SDIO_CK
PC3.GPIOParameters=GPIO_Label,GPIO_ModeDefaultEXTI
PC3.GPIO_Label=BUTTON_SELECT
PC3.GPIO_ModeDefaultEXTI=GPIO_MODE_IT_FALLING
PC3.Signal=GPXTI3
PC4.GPIOParameters=GPIO_Label
PC4.GPIO_Label=MUX2
PC4.Signal=GPIO_Output
PC5.GPIOParameters=GPIO_Label
PC5.GPIO_Label=MUX1
PC5.Signal=GPIO_Output
PC6.GPIOParameters=GPIO_Label
PC6.GPIO_Label=FAN_L_PWM
PC6.Signal=S_TIM3_CH1
PC7.GPIOParameters=GPIO_Label
PC7.GPIO_Label=FAN_R_PWM
PC7.Signal=S_TIM3_CH2
PC8.Mode=SD_1_bit
PC8.Signal=SDIO_D0
PC9.GPIOParameters=GPIO_Label
PC9.GPIO_Label=SDA
PC9.Mode=I2C
PC9.Signal=I2C3_SDA
PD2.Mode=SD_1_bit
PD2.Signal=SDIO_CMD
RCC.HSE_VALUE=25000000
RCC.SYSCLKFreq_VALUE=16000000
board=custom
